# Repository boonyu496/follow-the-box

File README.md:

# Follow the Box 当前项目资料

## 当前只看这些文档

| 文件 | 用途 |
|---|---|
| `FIRMWARE-SPEC.md` / `FIRMWARE-SPEC.html` | 固件代码框架总规范：VS Code 手写、AI 辅助、后续维护都按它写 |
| `CURRENT-PROJECT-ARCHITECTURE.md` | 当前项目架构地图：AP/局域网/云端 H5、固件运行链路、页面同步规则和问题定位入口 |
| `PIN-MAP-V1.md` | 当前唯一 Pin Map v1.0，所有代码和接线必须引用 |
| `ESTOP-FEEDBACK-CIRCUIT.md` | GPIO21 急停反馈隔离接线，禁止直读 36V 电门锁线 |
| `POLARITY-DEFINITIONS.md` | GPIO/MOS/光耦/控制器线极性定义 |
| `PWM-OUTPUT-CALIBRATION.md` | PWM→0-5V 油门频率、分辨率、映射公式、校准流程 |
| `protocols/` | DS600、UWB、H5、JY61P 协议/接口文件 |
| `CURRENT-PROJECT-SPEC.md` / `CURRENT-PROJECT-SPEC.html` | 项目总纲：目标、架构、安全、电源 |
| `CURRENT-PARTS-LIST.md` | 当前配件清单：已有、待补、线束分组 |
| `CURRENT-WIRING-AI.md` / `CURRENT-WIRING.html` | 当前接线方案：给 AI/给人看的接线说明 |
| `ASSEMBLY-WIRING-MINDMAP.html` | 当前中文接线思维导图：总接线、ESP32 引脚、分压/上拉/下拉/电容/急停反馈小电路 |
| `complete-wiring.svg` | 当前中文总接线 SVG 大图：模块关系总览，详细施工以思维导图和表格为准 |
| `complete-wiring-table.md` | 当前完整接线表：每个 ESP32 引脚、线束、电阻电容和模块端子 |
| `ASSEMBLY-WIRING-GUIDE.md` | 📦 装配接线完整流程图：按步骤装配思维导图 + 引脚速查表 + 上电顺序 |
| `OTA-UPDATE-SPEC.md` | OTA 正式发布规范：版本递增、构建、manifest/MD5、云端部署、H5 授权安装与失败排查 |
| `PERFBOARD-LAYOUT.html` / `PERFBOARD-LAYOUT.svg` | 当前 10×15cm 洞洞板元器件布局图；由 `gen_perfboard_layout.py` 生成并校验 |
| `CURRENT-BOX-DESIGN.md` | 控制盒外观、内部布局、接口、装配规则 |
| `CURRENT-FIRMWARE-SKILL-PLAN.md` | 固件模块、Profile、安装向导、测试计划、后续 skill 设计 |
| `CURRENT-FIRMWARE-ARCHITECTURE.md` / `CURRENT-FIRMWARE-ARCHITECTURE.html` | 固件代码架构：目录结构、模块边界、状态机、任务频率 |
| `skills/README.md` | 项目内 AI 技能包入口：给 Hermes/Claude/Copilot/其他 AI 调用，按 SaaS-Bench 风格执行开发、审查、排 bug、上电安全门控 |
| `.agents/skills/` | Codex 自动发现的轻量包装技能：负责快速触发、计划、锁定、diff 审查和云端 H5 部署隔离；详细技能仍在 `skills/` |
| `VERIFIED-LOCKS.md` | 已验证/安全关键方案锁定清单：板型、Pin Map、安全链、PWM 出口、UWB、OTA、云端 H5 部署、AI 技能门禁 |
| `AI-HANDOFF-MEMORY.md` | 项目内 AI 交接记忆：任何 AI 修改代码/架构/文档后，必须用 8-12 行短记录写清改动、验证、下一步 |
| `AI-AGENT-RUNBOOK.md` | Codex/Claude/Copilot/其他代码 AI 的固定启动 prompt 和交接记忆门禁；结束后运行 `python3 tools/check_ai_handoff.py` |
| `UWB-LEGACY-MIGRATION-REVIEW.md` | 旧 UWB 自动跟随项目迁移评估：可照抄/可借鉴/禁止照抄清单，以及 FollowBox 后续实施任务包 |
| `CLOUD-ASSIST-BACKLOG.md` | 后续云端困难场景协助待办：WiFi 上传 telemetry/图像，云端 AI/规则引擎给动作建议，ESP32 本地安全裁决 |
| `FOLLOWBOX-VISION-BACKLOG.md` | 三大远景待办：云训练/远程调试、云端轨迹记录→自动驾驶、自主交互(门检测/找人帮忙/买东西) |

## 文件归属与技能路由速查

| 文件/区域 | 先找谁 | 说明 |
|---|---|---|
| `CURRENT-PROJECT-ARCHITECTURE.md`, `FIRMWARE-SPEC.md`, `firmware/src/app/` | `skills/01-firmware-architecture-guardian` | 架构地图、模块边界、`main.cpp` 拆分和运行链路 |
| `firmware/src/safety/`, `firmware/src/control/`, `firmware/src/drive/` | `skills/03-safety-control-reviewer` | 安全门控、模式、混控、最终输出链；改动前看 `VERIFIED-LOCKS.md` |
| `PIN-MAP-V1.md`, `CURRENT-WIRING-AI.md`, `firmware/include/config/board_pins.h`, Profile | `skills/05-drive-power-calibration-engineer` | GPIO、电源、ADC、PWM、极性和校准；禁止旧 GPIO35/36/37/47/48 |
| `firmware/src/sensors/`, `protocols/` | `skills/04-sensor-protocol-integrator` | UWB/TOF/IMU/超声/雷达协议与 `SensorSnapshot` |
| `firmware/web/`, `firmware/src/web/`, `protocols/H5-API.md` | `skills/06-h5-telemetry-ui-engineer` | 车端 AP/局域网 H5；`firmware/data/` 只保留 tombstone，不是源码 |
| `cloud/`, `cloud/public/`, `cloud/firmware/`, `devspace.yaml` | `skills/06-h5-telemetry-ui-engineer` + `.agents/skills/followbox-cloud-h5-deploy` | 云端 H5、遥测、OTA 发布和 DevSpace；不能和车端 H5 混用部署 |
| `AI-HANDOFF-MEMORY.md`, `skills/`, `.agents/skills/`, `VERIFIED-LOCKS.md` | `skills/00-dispatcher`, `skills/07-code-review-debugger` | AI 交接、技能入口和锁检查；修改后必须跑门禁脚本 |
| `plans/cleanup/` | `skills/00-dispatcher` | 临时整理计划，完成或被新计划替代后可删除 |
| `output/`, `v/`, `zhiliao/` | `skills/07-code-review-debugger` | 历史证据/供应商资料/调试产物；先索引，不能第一轮盲删 |
| `firmware/.pio-core/`, `firmware/.pio/`, `vision_cam/.pio/`, `.codebuddy/db/` | `skills/07-code-review-debugger` | 本地可重建缓存；只在确认 ignored 后删除 |

## 当前硬件架构

```text
HOTRC DS600 接收机 PWM
  -> ESP32-S3-DevKitC-1
  -> PWM 转 0-5V 模拟量模块 ×2
  -> 左/右 36V 350W 有霍尔无刷控制器
  -> 左/右轮毂电机
```

辅助模块：

```text
UWB GC-P2304-GS-2 -> 跟随距离/方位
VL53L1X ×3 + TCA9548A -> 前向避障
HC-SR04 ×2 -> 左右侧辅助避障
JY61P -> 姿态/yaw 阻尼
ESP32-S3-CAM + OV5640 -> 独立视频
```

## 安全红线

- Antigravity P0 修订已写入 `FIRMWARE-SPEC.md`：GPIO35/36/37/47/48 不再作为电机驱动输出；急停反馈 GPIO21 必接；左右倒车线独立；需要预充/防火花；油门输出要死区/限幅/斜率控制。

- ESP32-S3 只接 5V/3.3V 和低压信号。
- ESP32-S3 没有真 DAC，左右油门必须通过 PWM 转 0-5V 模拟量模块。
- Schneider XB5AS542C 1NC 急停切控制器电门锁/使能线。
- 电机主电流不走洞洞板、排针、JST 小插头、杜邦线。
- DS600 PWM、HC-SR04 Echo、JY61P TX 若为 5V 信号，进 ESP32 前必须分压或电平转换；该物料属于 P0。
- 电池 ADC 统一使用 220k/10k 分压，覆盖 36V-60V；旧 130k/10k 在 48V 满电会超 ESP32 ADC 安全范围，禁止作为当前方案。
- 控制器 BAT- 主回路必须星型接地，转把 GND/ESP32 GND 只能作小电流参考，不能成为主负极断线后的回流路径。
- TCA9548A/VL53L1X I2C 必须外接 4.7k 上拉到 3.3V，固件必须实现 Bus Clear。
- JY61P 上电后必须静止 3 秒；UWB 与 DC-DC/Buck 至少保持 50mm 并做 5V 输出滤波。
- 10×15cm 洞洞板布局以 `PERFBOARD-LAYOUT.html` / `PERFBOARD-LAYOUT.svg` 为准；实际接线以 `ASSEMBLY-WIRING-MINDMAP.html`、`complete-wiring.svg` 和 `complete-wiring-table.md` 为准。旧错误 SVG/JSON 图作废，不能再引用。
- GPIO14/15/16/39 只能驱动 MOS/光耦/继电器输入，未装 MOS/光耦前禁止接控制器开关量线。
- GPIO21 急停反馈必须用第二触点干接点或光耦隔离，禁止直接读取 36V 电门锁线。
- ESP32-S3-CAM 只做视频，不做主控。
- 首次调试必须架空车轮。

## 下一步

1. 补齐 `CURRENT-PARTS-LIST.md` 里的 P0 物料。
2. 到货后拍 DS600 接收机、无刷控制器线标、轮毂电机线束、电池铭牌、急停背面。
3. 按 `CURRENT-WIRING-AI.md` 分阶段上电。
4. 写代码时以 `FIRMWARE-SPEC.md` 为唯一代码框架依据；不符合它的实现需要重构。
5. 让任何 AI 参与开发/审查/排 bug 前，先读 `.agents/skills/` 包装、`skills/README.md` 和 `VERIFIED-LOCKS.md`，再按路由加载对应 `skills/*/SKILL.md`。
6. 任何 AI 修改代码、架构、文档、Profile、协议或技能后，必须在 `AI-HANDOFF-MEMORY.md` 顶部追加 8-12 行短交接记录。
7. 用 Codex/Claude/Copilot/其他代码 AI 前先读 `AI-AGENT-RUNBOOK.md`；任务结束后运行 `python3 tools/check_ai_handoff.py` 和 `python3 tools/check_verified_locks.py`，不通过或未解释 warning 就不能算完成。

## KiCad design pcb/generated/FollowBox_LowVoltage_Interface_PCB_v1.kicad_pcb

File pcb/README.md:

# FollowBox low-voltage PCB starter

This directory contains the simplest import path for drawing the Follow the Box low-voltage interface PCB in JLC EasyEDA Pro:

1. Generate a KiCad PCB file from the project pin map.
2. Import the generated `.kicad_pcb` or `.zip` into JLC EasyEDA Pro with `Import KiCad`.
3. Use EasyEDA Pro for final symbol/footprint replacement, DRC, routing, and ordering.

The generated board is a low-voltage signal/interface starter only. It intentionally excludes motor BAT+/BAT-, controller main current, and motor phase wires.

## Files

- `generate_followbox_kicad_pcb.py` - deterministic generator for a starter PCB layout.
- `generated/FollowBox_LowVoltage_Interface_PCB_v1.kicad_pcb` - generated KiCad PCB file.
- `generated/FollowBox_LowVoltage_Interface_PCB_v1.zip` - import package for EasyEDA Pro.

## Regenerate

```powershell
python .\pcb\generate_followbox_kicad_pcb.py
```

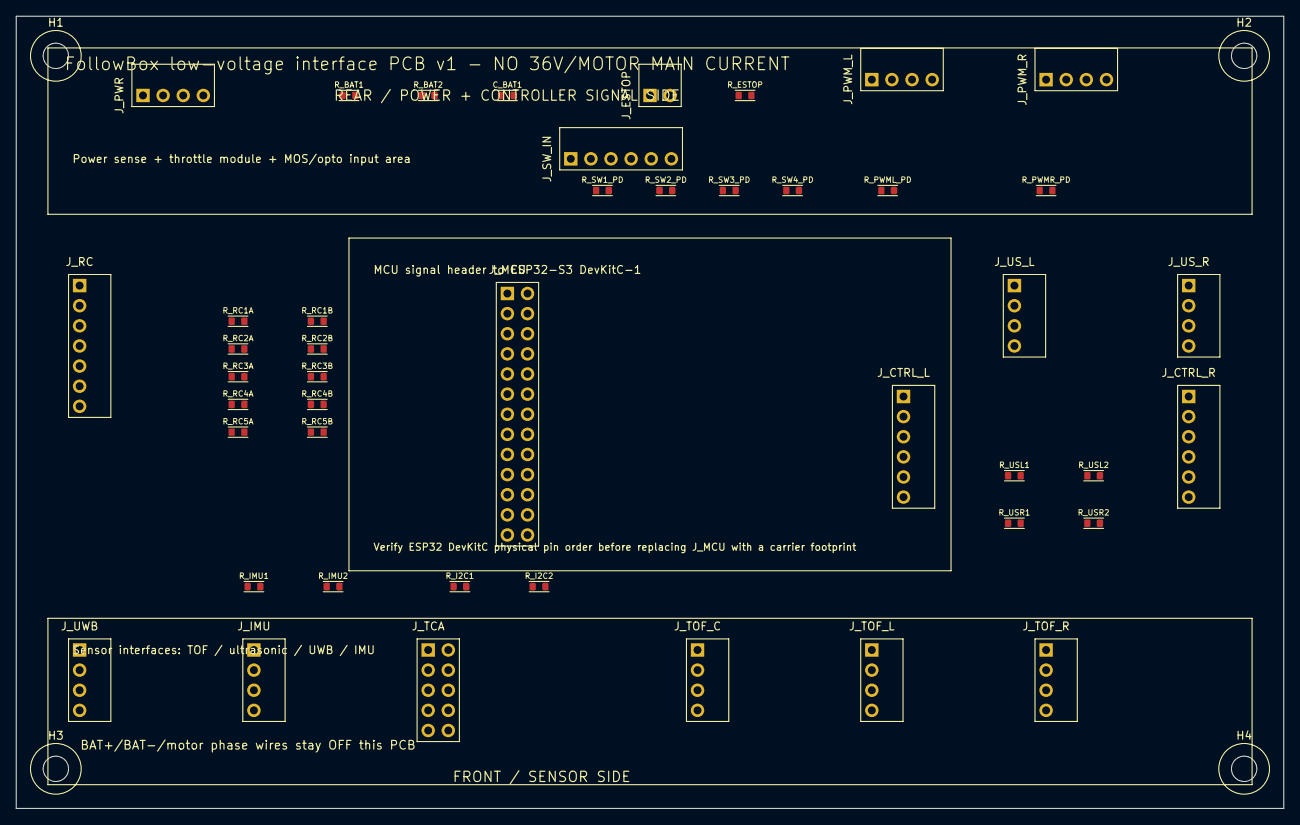
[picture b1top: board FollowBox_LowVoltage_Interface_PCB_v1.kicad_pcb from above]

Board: 2 copper layers, 160.0 x 100.0 mm, 49 parts (0 on the bottom side), 45 nets, no tracks yet.

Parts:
C_BAT1: 0.1uF; R_0603_1608Metric
H1, H2, H3, H4: MountingHole_3.2mm
J_CTRL_L: CTRL L signals; PinHeader_1x6_P2.54mm
J_CTRL_R: CTRL R signals; PinHeader_1x6_P2.54mm
J_ESTOP: ESTOP second NC; PinHeader_1x2_P2.54mm
J_IMU: JY61P IMU; PinHeader_1x4_P2.54mm
J_MCU: ESP32-S3 signal harness; PinHeader_2x13_P2.54mm
J_PWM_L: Left PWM-0/5V module; PinHeader_1x4_P2.54mm
J_PWM_R: Right PWM-0/5V module; PinHeader_1x4_P2.54mm
J_PWR: 5V bus + battery sense; PinHeader_1x4_P2.54mm
J_RC: DS600 CH1-CH5 + power; PinHeader_1x7_P2.54mm
J_SW_IN: MOS/opto input module; PinHeader_1x6_P2.54mm
J_TCA: TCA9548A module; PinHeader_2x5_P2.54mm
J_TOF_C: TOF center; PinHeader_1x4_P2.54mm
J_TOF_L: TOF left; PinHeader_1x4_P2.54mm
J_TOF_R: TOF right; PinHeader_1x4_P2.54mm
J_US_L: HC-SR04 left; PinHeader_1x4_P2.54mm
J_US_R: HC-SR04 right; PinHeader_1x4_P2.54mm
J_UWB: GC-P2304 UWB; PinHeader_1x4_P2.54mm
R_BAT1: 220k; R_0603_1608Metric
R_BAT2: 10k; R_0603_1608Metric
R_ESTOP: 10k; R_0603_1608Metric
R_I2C1, R_I2C2: 4.7k; R_0603_1608Metric
R_IMU1: 10k; R_0603_1608Metric
R_IMU2: 20k; R_0603_1608Metric
R_PWML_PD: 10k; R_0603_1608Metric
R_PWMR_PD: 10k; R_0603_1608Metric
R_RC1A, R_RC2A, R_RC3A, R_RC4A, R_RC5A: 10k; R_0603_1608Metric
R_RC1B, R_RC2B, R_RC3B, R_RC4B, R_RC5B: 20k; R_0603_1608Metric
R_SW1_PD, R_SW2_PD, R_SW3_PD, R_SW4_PD: 10k; R_0603_1608Metric
R_USL1: 10k; R_0603_1608Metric
R_USL2: 20k; R_0603_1608Metric
R_USR1: 10k; R_0603_1608Metric
R_USR2: 20k; R_0603_1608Metric

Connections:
+3V3: J_MCU.3 (+3V3), J_PWR.3 (+3V3), J_TCA.1 (+3V3), J_TOF_C.1 (+3V3), J_TOF_L.1 (+3V3), J_TOF_R.1 (+3V3), J_UWB.1 (+3V3), R_ESTOP.1, R_I2C1.1, R_I2C2.1
+5V: J_IMU.1 (+5V), J_MCU.2 (+5V), J_PWR.1 (+5V), J_RC.1 (+5V), J_SW_IN.6 (+5V), J_US_L.1 (+5V), J_US_R.1 (+5V)
BAT_SENSE_RAW: J_PWR.4 (BAT_SENSE_RAW), R_BAT1.1
BRAKE_SW: J_CTRL_L.4 (BRAKE_SW), J_CTRL_R.4 (BRAKE_SW)
CTRL_L_5V: J_CTRL_L.1 (CTRL_L_5V), J_PWM_L.3 (CTRL_L_5V)
CTRL_R_5V: J_CTRL_R.1 (CTRL_R_5V), J_PWM_R.3 (CTRL_R_5V)
ENABLE_SW: J_CTRL_L.6 (ENABLE_SW), J_CTRL_R.6 (ENABLE_SW)
GND: C_BAT1.2, J_ESTOP.2 (GND), J_IMU.2 (GND), J_MCU.1 (GND), J_MCU.26 (GND), J_PWM_L.2 (GND), J_PWM_R.2 (GND), J_PWR.2 (GND), J_RC.2 (GND), J_SW_IN.1 (GND), J_TCA.2 (GND), J_TOF_C.2 (GND), J_TOF_L.2 (GND), J_TOF_R.2 (GND), J_US_L.2 (GND), J_US_R.2 (GND), J_UWB.2 (GND), R_BAT2.2, R_IMU2.2, R_PWML_PD.2, R_PWMR_PD.2, R_RC1B.2, R_RC2B.2, R_RC3B.2, R_RC4B.2, R_RC5B.2, R_SW1_PD.2, R_SW2_PD.2, R_SW3_PD.2, R_SW4_PD.2, R_USL2.2, R_USR2.2
GPIO1_BAT_ADC: C_BAT1.1, J_MCU.4 (GPIO1_BAT_ADC), R_BAT1.2, R_BAT2.1
GPIO4_RC_CH1: J_MCU.6 (GPIO4_RC_CH1), R_RC1A.2, R_RC1B.1
GPIO5_RC_CH2: J_MCU.7 (GPIO5_RC_CH2), R_RC2A.2, R_RC2B.1
GPIO6_RC_CH3: J_MCU.8 (GPIO6_RC_CH3), R_RC3A.2, R_RC3B.1
GPIO7_RC_CH4: J_MCU.9 (GPIO7_RC_CH4), R_RC4A.2, R_RC4B.1
GPIO8_RC_CH5: J_MCU.10 (GPIO8_RC_CH5), R_RC5A.2, R_RC5B.1
GPIO9_US_TRIG: J_MCU.11 (GPIO9_US_TRIG), J_US_L.3 (GPIO9_US_TRIG), J_US_R.3 (GPIO9_US_TRIG)
GPIO10_I2C_SDA: J_MCU.12 (GPIO10_I2C_SDA), J_TCA.3 (SDA), R_I2C1.2
GPIO11_I2C_SCL: J_MCU.13 (GPIO11_I2C_SCL), J_TCA.4 (SCL), R_I2C2.2
GPIO12_PWM_L: J_MCU.14 (GPIO12_PWM_L), J_PWM_L.1 (GPIO12_PWM_L), R_PWML_PD.1
GPIO13_PWM_R: J_MCU.15 (GPIO13_PWM_R), J_PWM_R.1 (GPIO13_PWM_R), R_PWMR_PD.1
GPIO14_BRAKE_OUT: J_MCU.16 (GPIO14_BRAKE_OUT), J_SW_IN.2 (GPIO14_BRAKE_OUT), R_SW1_PD.1
GPIO15_REV_L: J_MCU.17 (GPIO15_REV_L), J_SW_IN.3 (GPIO15_REV_L), R_SW2_PD.1
GPIO16_REV_R: J_MCU.18 (GPIO16_REV_R), J_SW_IN.4 (GPIO16_REV_R), R_SW3_PD.1
GPIO17_UWB_TX: J_MCU.19 (GPIO17_UWB_TX), J_UWB.3 (UWB_RX)
GPIO18_UWB_RX: J_MCU.20 (GPIO18_UWB_RX), J_UWB.4 (UWB_TX)
GPIO21_ESTOP_FB: J_ESTOP.1 (GPIO21_ESTOP_FB), J_MCU.21 (GPIO21_ESTOP_FB), R_ESTOP.2
GPIO39_ENABLE_OUT: J_MCU.22 (GPIO39_ENABLE_OUT), J_SW_IN.5 (GPIO39_ENABLE_OUT), R_SW4_PD.1
GPIO40_US_ECHO_L: J_MCU.23 (GPIO40_US_ECHO_L), R_USL1.2, R_USL2.1
GPIO41_US_ECHO_R: J_MCU.24 (GPIO41_US_ECHO_R), R_USR1.2, R_USR2.1
GPIO42_IMU_RX: J_MCU.25 (GPIO42_IMU_RX), R_IMU1.2, R_IMU2.1
IMU_TX_RAW: J_IMU.3 (IMU_TX_RAW), R_IMU1.1
RC_CH1_RAW: J_RC.3 (RC_CH1_RAW), R_RC1A.1
RC_CH2_RAW: J_RC.4 (RC_CH2_RAW), R_RC2A.1
RC_CH3_RAW: J_RC.5 (RC_CH3_RAW), R_RC3A.1
RC_CH4_RAW: J_RC.6 (RC_CH4_RAW), R_RC4A.1
RC_CH5_RAW: J_RC.7 (RC_CH5_RAW), R_RC5A.1
TCA_SC0: J_TCA.6 (TCA_SC0), J_TOF_C.4 (SCL)
TCA_SC1: J_TCA.8 (TCA_SC1), J_TOF_L.4 (SCL)
TCA_SC2: J_TCA.10 (TCA_SC2), J_TOF_R.4 (SCL)
TCA_SD0: J_TCA.5 (TCA_SD0), J_TOF_C.3 (SDA)
TCA_SD1: J_TCA.7 (TCA_SD1), J_TOF_L.3 (SDA)
TCA_SD2: J_TCA.9 (TCA_SD2), J_TOF_R.3 (SDA)
THR_L_OUT: J_CTRL_L.3 (THR_L_OUT), J_PWM_L.4 (THR_L_OUT)
THR_R_OUT: J_CTRL_R.3 (THR_R_OUT), J_PWM_R.4 (THR_R_OUT)
US_ECHO_L_RAW: J_US_L.4 (US_ECHO_L_RAW), R_USL1.1
US_ECHO_R_RAW: J_US_R.4 (US_ECHO_R_RAW), R_USR1.1

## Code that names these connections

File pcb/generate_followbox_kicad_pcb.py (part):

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    # Central MCU wiring header. This avoids guessing the exact DevKitC physical pin order.
    mcu_pads = [
        pad(1, "GND"), pad(2, "+5V"),
        pad(3, "+3V3"), pad(4, "GPIO1_BAT_ADC"),
        pad(5, "GPIO2_FAULT_IN"), pad(6, "GPIO4_RC_CH1"),
        pad(7, "GPIO5_RC_CH2"), pad(8, "GPIO6_RC_CH3"),
        pad(9, "GPIO7_RC_CH4"), pad(10, "GPIO8_RC_CH5"),
        pad(11, "GPIO9_US_TRIG"), pad(12, "GPIO10_I2C_SDA"),
        pad(13, "GPIO11_I2C_SCL"), pad(14, "GPIO12_PWM_L"),
        pad(15, "GPIO13_PWM_R"), pad(16, "GPIO14_BRAKE_OUT"),
        pad(17, "GPIO15_REV_L"), pad(18, "GPIO16_REV_R"),
        pad(19, "GPIO17_UWB_TX"), pad(20, "GPIO18_UWB_RX"),
        pad(21, "GPIO21_ESTOP_FB"), pad(22, "GPIO39_ENABLE_OUT"),
        pad(23, "GPIO40_US_ECHO_L"), pad(24, "GPIO41_US_ECHO_R"),
        pad(25, "GPIO42_IMU_RX"), pad(26, "GND"),
    ]
    pcb.pin_header("J_MCU", "ESP32-S3 signal harness", 62, 35, mcu_pads, cols=2)

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        pcb.resistor(f"R_RC{idx}B", "20k", 38, y, f"GPIO{gpio}_RC_CH{idx}", "GND")

    # Sensor connectors.
    pcb.pin_header("J_UWB", "GC-P2304 UWB", 8, 80, [pad(1, "+3V3"), pad(2, "GND"), pad(3, "GPIO17_UWB_TX", "UWB_RX"), pad(4, "GPIO18_UWB_RX", "UWB_TX")])
    pcb.pin_header("J_IMU", "JY61P IMU", 30, 80, [pad(1, "+5V"), pad(2, "GND"), pad(3, "IMU_TX_RAW"), pad(4, "")])
    pcb.resistor("R_IMU1", "10k", 30, 72, "IMU_TX_RAW", "GPIO42_IMU_RX")
    pcb.resistor("R_IMU2", "20k", 40, 72, "GPIO42_IMU_RX", "GND")

    # TCA9548A module and three VL53L1X downstream ports.
    pcb.pin_header("J_TCA", "TCA9548A module", 52, 80, [
        pad(1, "+3V3"), pad(2, "GND"), pad(3, "GPIO10_I2C_SDA", "SDA"), pad(4, "GPIO11_I2C_SCL", "SCL"),
        pad(5, "TCA_SD0"), pad(6, "TCA_SC0"), pad(7, "TCA_SD1"), pad(8, "TCA_SC1"), pad(9, "TCA_SD2"), pad(10, "TCA_SC2"),
    ], cols=2)
    pcb.resistor("R_I2C1", "4.7k", 56, 72, "+3V3", "GPIO10_I2C_SDA")
    pcb.resistor("R_I2C2", "4.7k", 66, 72, "+3V3", "GPIO11_I2C_SCL")
    pcb.pin_header("J_TOF_C", "TOF center", 86, 80, [pad(1, "+3V3"), pad(2, "GND"), pad(3, "TCA_SD0", "SDA"), pad(4, "TCA_SC0", "SCL")])
    pcb.pin_header("J_TOF_L", "TOF left", 108, 80, [pad(1, "+3V3"), pad(2, "GND"), pad(3, "TCA_SD1", "SDA"), pad(4, "TCA_SC1", "SCL")])
    pcb.pin_header("J_TOF_R", "TOF right", 130, 80, [pad(1, "+3V3"), pad(2, "GND"), pad(3, "TCA_SD2", "SDA"), pad(4, "TCA_SC2", "SCL")])

    # Ultrasonic connectors and Echo dividers.
    pcb.pin_header("J_US_L", "HC-SR04 left", 126, 34, [pad(1, "+5V"), pad(2, "GND"), pad(3, "GPIO9_US_TRIG"), pad(4, "US_ECHO_L_RAW")])
    pcb.pin_header("J_US_R", "HC-SR04 right", 148, 34, [pad(1, "+5V"), pad(2, "GND"), pad(3, "GPIO9_US_TRIG"), pad(4, "US_ECHO_R_RAW")])
    pcb.resistor("R_USL1", "10k", 126, 58, "US_ECHO_L_RAW", "GPIO40_US_ECHO_L")
    pcb.resistor("R_USL2", "20k", 136, 58, "GPIO40_US_ECHO_L", "GND")
    pcb.resistor("R_USR1", "10k", 126, 64, "US_ECHO_R_RAW", "GPIO41_US_ECHO_R")
    pcb.resistor("R_USR2", "20k", 136, 64, "GPIO41_US_ECHO_R", "GND")

    # Power input/sense and estop feedback.
    pcb.pin_header("J_PWR", "5V bus + battery sense", 16, 10, [pad(1, "+5V"), pad(2, "GND"), pad(3, "+3V3"), pad(4, "BAT_SENSE_RAW")], rot=90)
    pcb.resistor("R_BAT1", "220k", 42, 10, "BAT_SENSE_RAW", "GPIO1_BAT_ADC")
    pcb.resistor("R_BAT2", "10k", 52, 10, "GPIO1_BAT_ADC", "GND")
    pcb.capacitor("C_BAT1", "0.1uF", 62, 10, "GPIO1_BAT_ADC", "GND")
    pcb.pin_header("J_ESTOP", "ESTOP second NC", 80, 10, [pad(1, "GPIO21_ESTOP_FB"), pad(2, "GND")], rot=90)
    pcb.resistor("R_ESTOP", "10k", 92, 10, "+3V3", "GPIO21_ESTOP_FB")

    # Throttle PWM module interfaces and controller signal connectors.
    pcb.pin_header("J_PWM_L", "Left PWM-0/5V module", 108, 8, [pad(1, "GPIO12_PWM_L"), pad(2, "GND"), pad(3, "CTRL_L_5V"), pad(4, "THR_L_OUT")], rot=90)
    pcb.pin_header("J_PWM_R", "Right PWM-0/5V module", 130, 8, [pad(1, "GPIO13_PWM_R"), pad(2, "GND"), pad(3, "CTRL_R_5V"), pad(4, "THR_R_OUT")], rot=90)
    pcb.resistor("R_PWML_PD", "10k", 110, 22, "GPIO12_PWM_L", "GND")
    pcb.resistor("R_PWMR_PD", "10k", 130, 22, "GPIO13_PWM_R", "GND")
    pcb.pin_header("J_CTRL_L", "CTRL L signals", 112, 48, [pad(1, "CTRL_L_5V"), pad(2, "CTRL_L_GND"), pad(3, "THR_L_OUT"), pad(4, "BRAKE_SW"), pad(5, "REV_L_SW"), pad(6, "ENABLE_SW")])
    pcb.pin_header("J_CTRL_R", "CTRL R signals", 148, 48, [pad(1, "CTRL_R_5V"), pad(2, "CTRL_R_GND"), pad(3, "THR_R_OUT"), pad(4, "BRAKE_SW"), pad(5, "REV_R_SW"), pad(6, "ENABLE_SW")])

    # MOS/opto input header. Output side is intentionally external/isolated.
    pcb.pin_header("J_SW_IN", "MOS/opto input module", 70, 18, [
        pad(1, "GND"), pad(2, "GPIO14_BRAKE_OUT"), pad(3, "GPIO15_REV_L"), pad(4, "GPIO16_REV_R"), pad(5, "GPIO39_ENABLE_OUT"), pad(6, "+5V"),
    ], rot=90)
    for idx, gpio_net in enumerate(["GPIO14_BRAKE_OUT", "GPIO15_REV_L", "GPIO16_REV_R", "GPIO39_ENABLE_OUT"]):
        pcb.resistor(f"R_SW{idx + 1}_PD", "10k", 74 + idx * 8, 22, gpio_net, "GND")

    pcb.gr_text("warn1", "BAT+/BAT-/motor phase wires stay OFF this PCB", 8, 92, 1.1)
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
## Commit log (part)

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2026-06-16 首次提交：Follow the Box 项目完整代码
2026-06-17 chore: deploy followbox 2026-06-17 21:44
2026-06-17 chore: deploy followbox 2026-06-17 22:55
2026-06-18 chore: deploy followbox 2026-06-18 12:52
2026-06-18 chore: deploy followbox 2026-06-18 17:05
2026-06-18 chore: deploy followbox 2026-06-18 19:54
2026-06-18 chore: deploy followbox 2026-06-18 21:10
2026-06-18 fix: repair control center startup and safe sync flow
2026-06-18 refactor: move local control center out of tracked tools
2026-06-19 chore: deploy followbox 2026-06-18 23:50
2026-06-19 chore: deploy followbox 2026-06-19 22:44
2026-06-19 chore: deploy followbox 2026-06-20 00:34
2026-06-20 chore: deploy followbox 2026-06-20 15:45
2026-06-20 chore: deploy followbox 2026-06-20 16:19
2026-06-20 chore: deploy followbox 2026-06-20 16:36
2026-06-20 chore: manual push 2026-06-20
2026-06-20 chore: deploy followbox 2026-06-20_20:50
2026-06-20 chore: deploy followbox 2026-06-20_21:04
2026-06-21 chore: deploy followbox 2026-06-21_16:51
2026-06-21 chore: deploy followbox 2026-06-21 22:40
2026-06-22 chore: deploy followbox 2026-06-22_18:26
2026-06-22 chore: deploy followbox 2026-06-22 21:07
2026-06-24 chore: deploy followbox 2026-06-24_10:37
2026-06-24 chore: deploy followbox 2026-06-24 15:29
2026-06-25 chore: deploy followbox 2026-06-25 09:33
2026-06-26 chore: deploy followbox 2026.06.26-rc-drive-fault-pullup.1
2026-06-27 chore: 定期推送
2026-06-29 chore: deploy followbox 2026-06-28 23:45
2026-06-30 cleanup project structure and artifacts
